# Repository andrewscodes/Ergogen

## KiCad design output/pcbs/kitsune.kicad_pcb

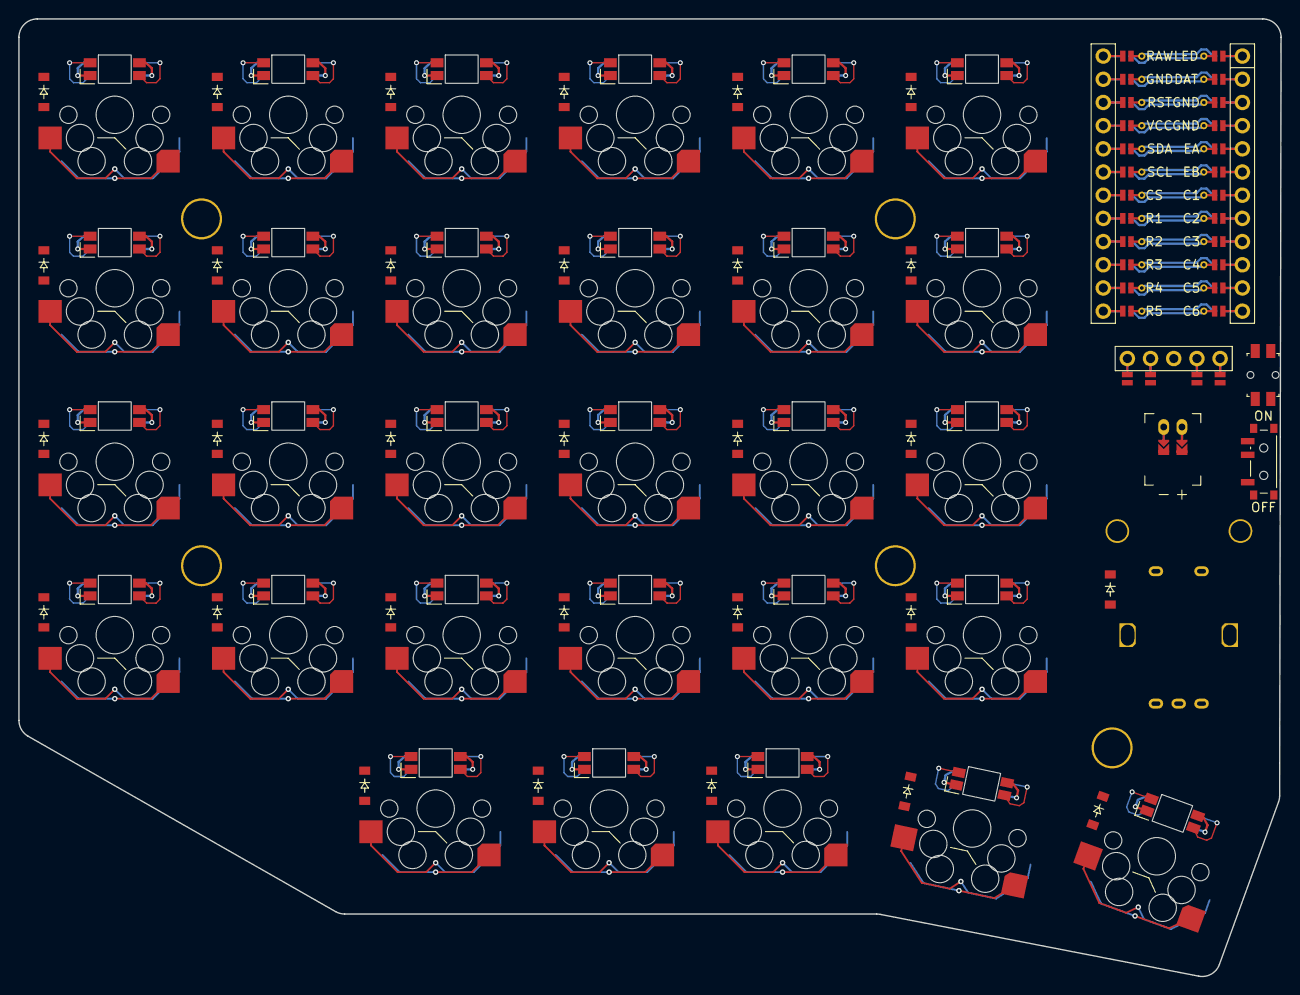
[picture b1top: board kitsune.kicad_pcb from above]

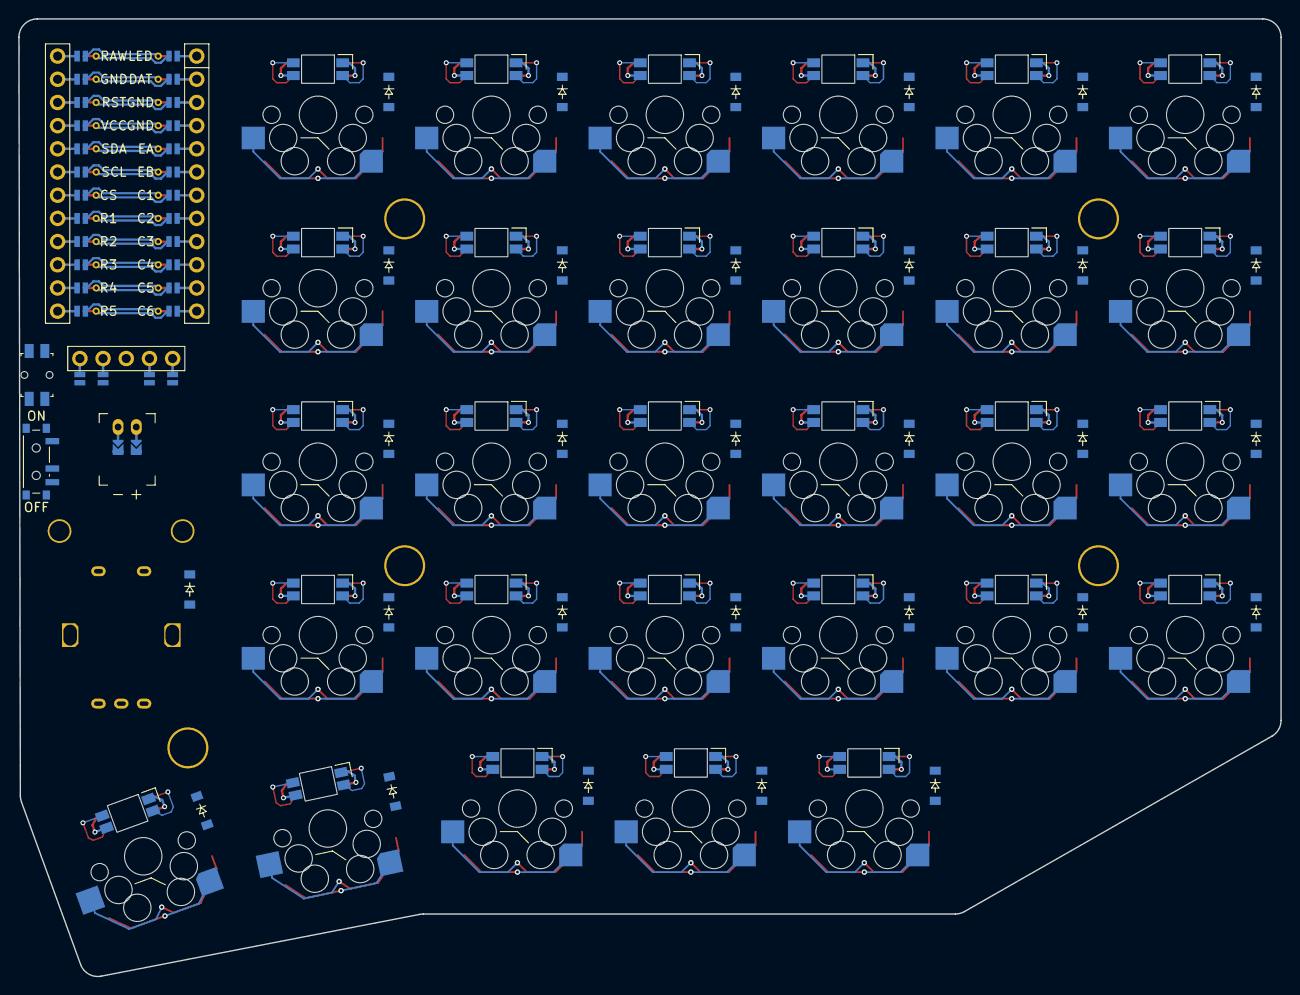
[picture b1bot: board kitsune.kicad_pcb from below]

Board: 2 copper layers, 138.3 x 104.9 mm, 101 parts (58 on the bottom side), 86 nets.

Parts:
D1, D2, D3, D4, D5, D6, D7, D8, D9, D10, D11, D12, D13, D14, D15, D16, D17, D18, D19, D20, D21, D22, D23, D24, D25, D26, D27, D28, D29, D30: diode_tht_sod123
DISP1: display_nice_view
JST1: battery_connector_jst_ph_2
LED1, LED2, LED3, LED4, LED5, LED6, LED7, LED8, LED9, LED10, LED11, LED12, LED13, LED14, LED15, LED16, LED17, LED18, LED19, LED20, LED21, LED22, LED23, LED24, LED25, LED26, LED27, LED28, LED29: led_SK6812mini-e (per-key, reversible)
MCU1: mcu_nice_nano
MH1, MH2, MH3, MH4, MH5, MH6, MH7: mounting_hole_npth
PWR1: power_switch_smd_side
RE1: rotary_encoder_ec11_ec12
RST1: reset_switch_smd_side
S1, S2, S3, S4, S5, S6, S7, S8, S9, S10, S11, S12, S13, S14, S15, S16, S17, S18, S19, S20, S21, S22, S23, S24, S25, S26, S27, S28, S29: switch_mx

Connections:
BAT_P: JST1.1, PWR1.1, PWR1.3
C1: MCU1.107, S1.1, S2.1, S3.1, S4.1, S25.1
C2: MCU1.108, S5.1, S6.1, S7.1, S8.1, S26.1
C3: MCU1.109, S9.1, S10.1, S11.1, S12.1, S27.1
C4: MCU1.110, S13.1, S14.1, S15.1, S16.1, S28.1
C5: MCU1.111, S17.1, S18.1, S19.1, S20.1, S29.1
C6: MCU1.112, RE1.S1, S21.1, S22.1, S23.1, S24.1
CS: DISP1.10, DISP1.20, MCU1.118
DISP1_1: DISP1.1, DISP1.14, DISP1.27
DISP1_2: DISP1.2, DISP1.15, DISP1.26
DISP1_4: DISP1.4, DISP1.16, DISP1.25
DISP1_5: DISP1.5, DISP1.17, DISP1.24
EA: MCU1.105, RE1.A
EB: MCU1.106, RE1.C
GND: DISP1.11, DISP1.21, JST1.2, LED1.3, LED2.3, LED3.3, LED4.3, LED5.3, LED6.3, LED7.3, LED8.3, LED9.3, LED10.3, LED11.3, LED12.3, LED13.3, LED14.3, LED15.3, LED16.3, LED17.3, LED18.3, LED19.3, LED20.3, LED21.3, LED22.3, LED23.3, LED24.3, LED25.3, LED26.3, LED27.3, LED28.3, LED29.3, MCU1.103, MCU1.104, MCU1.123, RE1.B, RST1.1, RST1.3
JST1_1: JST1.11, JST1.21, JST1.31
JST1_2: JST1.12, JST1.22, JST1.32
LED: LED4.4, MCU1.101
LED1: LED4.2, LED8.4
LED2: LED8.2, LED12.4
LED3: LED12.2, LED16.4
LED4: LED16.2, LED20.4
LED5: LED20.2, LED24.4
LED6: LED23.4, LED24.2
LED7: LED19.4, LED23.2
LED8: LED15.4, LED19.2
LED9: LED11.4, LED15.2
LED10: LED7.4, LED11.2
LED11: LED3.4, LED7.2
LED12: LED2.4, LED3.2
LED13: LED2.2, LED6.4
LED14: LED6.2, LED10.4
LED15: LED10.2, LED14.4
LED16: LED14.2, LED18.4
LED17: LED18.2, LED22.4
LED18: LED21.4, LED22.2
LED19: LED17.4, LED21.2
LED20: LED13.4, LED17.2
LED21: LED9.4, LED13.2
LED22: LED5.4, LED9.2
LED23: LED1.4, LED5.2
LED24: LED1.2, LED25.4
LED25: LED25.2, LED26.4
LED26: LED26.2, LED27.4
LED27: LED27.2, LED28.4
LED28: LED28.2, LED29.4
R1: D4.1, D8.1, D12.1, D16.1, D20.1, D24.1, MCU1.117
R2: D3.1, D7.1, D11.1, D15.1, D19.1, D23.1, MCU1.116
R3: D2.1, D6.1, D10.1, D14.1, D18.1, D22.1, MCU1.115
R4: D1.1, D5.1, D9.1, D13.1, D17.1, D21.1, MCU1.114
R5: D25.1, D26.1, D27.1, D28.1, D29.1, D30.1, MCU1.113
RAW: MCU1.124, PWR1.2
RST: MCU1.122, RST1.2, RST1.4
SCL: DISP1.12, DISP1.22, MCU1.119
SDA: DISP1.13, DISP1.23, MCU1.120
VCC: DISP1.3, LED1.1, LED2.1, LED3.1, LED4.1, LED5.1, LED6.1, LED7.1, LED8.1, LED9.1, LED10.1, LED11.1, LED12.1, LED13.1, LED14.1, LED15.1, LED16.1, LED17.1, LED18.1, LED19.1, LED20.1, LED21.1, LED22.1, LED23.1, LED24.1, LED25.1, LED26.1, LED27.1, LED28.1, LED29.1, MCU1.121
endiode: D30.2, RE1.S2
fifth_five: D29.2, S29.2
first_five: D25.2, S25.2
five_four: D17.2, S17.2
five_one: D20.2, S20.2
five_three: D18.2, S18.2
five_two: D19.2, S19.2
four_four: D13.2, S13.2
four_one: D16.2, S16.2
four_three: D14.2, S14.2
four_two: D15.2, S15.2
fourth_five: D28.2, S28.2
one_four: D1.2, S1.2
one_one: D4.2, S4.2
one_three: D2.2, S2.2
one_two: D3.2, S3.2
second_five: D26.2, S26.2
six_four: D21.2, S21.2
six_one: D24.2, S24.2
six_three: D22.2, S22.2
six_two: D23.2, S23.2
third_five: D27.2, S27.2
three_four: D9.2, S9.2
three_one: D12.2, S12.2
three_three: D10.2, S10.2
three_two: D11.2, S11.2
two_four: D5.2, S5.2
two_one: D8.2, S8.2
two_three: D6.2, S6.2
two_two: D7.2, S7.2

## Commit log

2025-08-19 pcb created
2025-08-22 changed reset switch x position
2025-09-02 refactor: update component references to include 'ceoloide/' prefix
2025-09-05 fix: adjust thumb reference shifts for improved alignment
